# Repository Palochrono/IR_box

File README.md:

# IR_box
Normally open (HIGH) keychron low profile optical hitbox
Keychron switches footprint from [here](https://github.com/girishji/keychron-optical-keyboard?tab=MIT-1-ov-file)
## Part list
| Component | Description | Number_used |
| --------------- | --------------- | --------------- |
| R_IR | 180 $\Omega$ 0805 | 16 |
| R_PT | 2k $\Omega$ 0603 | 16 |
| Phototransistor | 0805 | 16 |
| IR_led | 0805 | 16 |
| Rp2040-zero | Waveshare | 1 |
| Pushbutton | 6*6mm | 4 |
| Key switches | Keychron optical low profile | 16 |
| OLED display | 0.96 inch I2C SSD1306 | 1 |
| Keycap set | DOIO KCGM-02 KCGM-03| 1 |
## Schematics and Render
Half-vias used to use the extra pins in rp2040-zero

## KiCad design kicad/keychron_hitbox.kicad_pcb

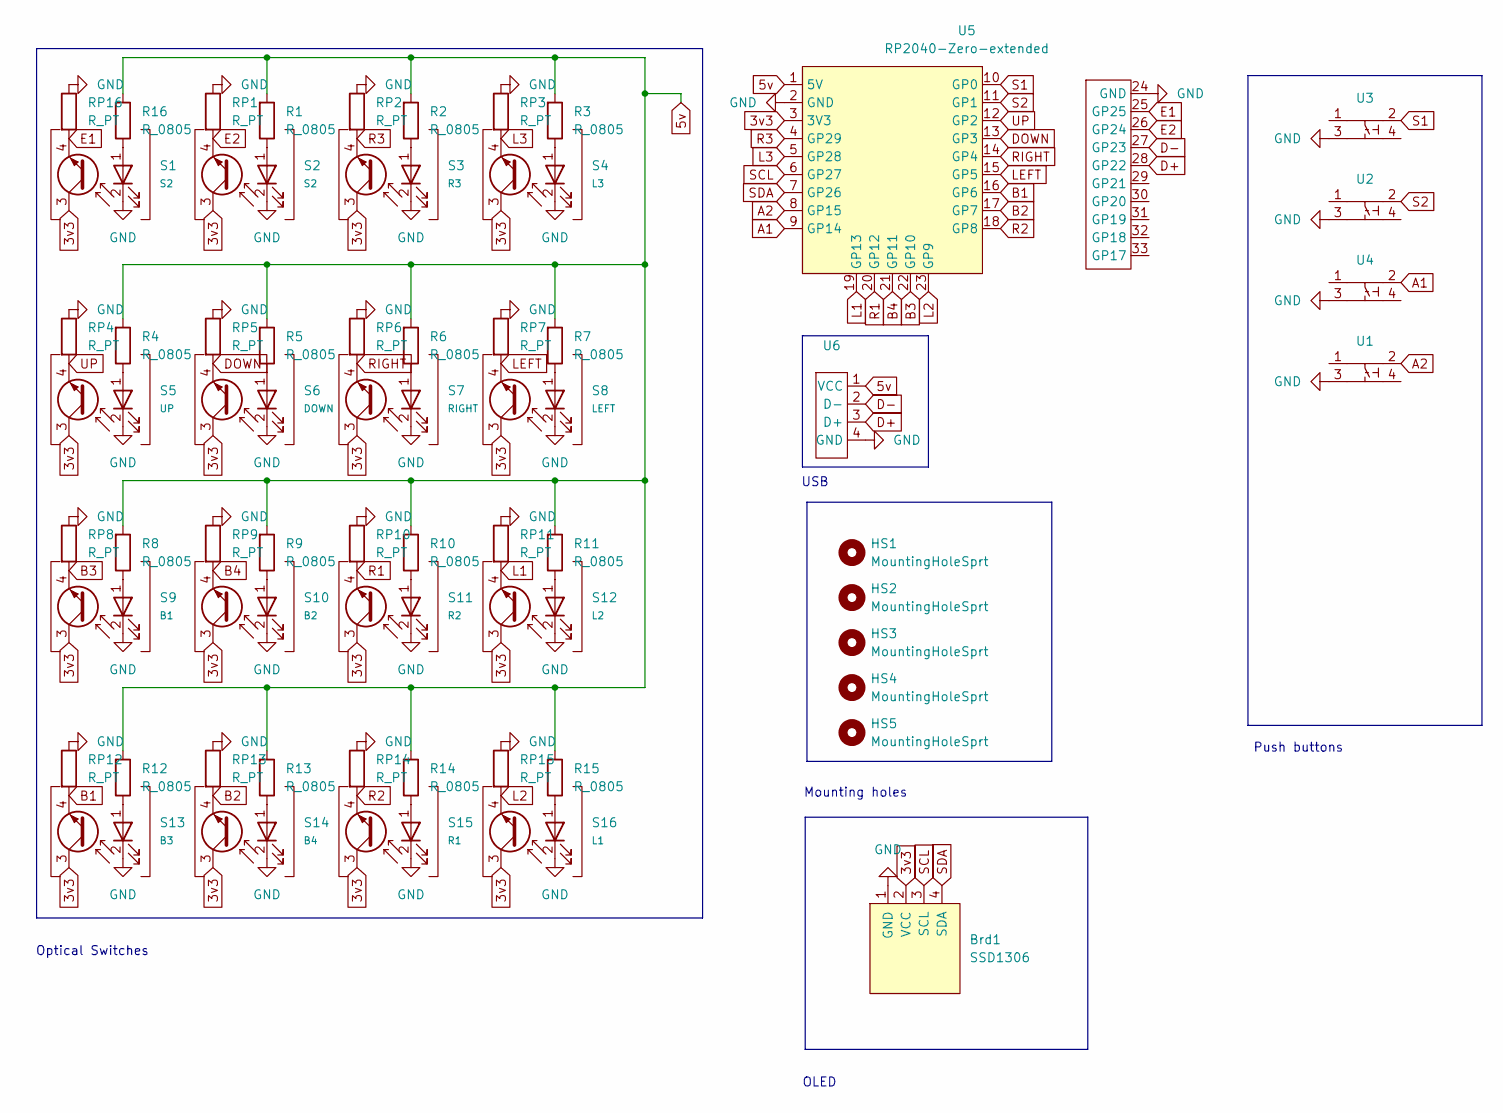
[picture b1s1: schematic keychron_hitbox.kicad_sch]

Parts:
Brd1: SSD1306; 128x64OLED_hollowed
HS1, HS2, HS3, HS4, HS5: MountingHoleSprt; MountingHole_2.2mm_M2_ISO7380_Pad
R1, R2, R3, R4, R5, R6, R7, R8, R9, R10, R11, R12, R13, R14, R15, R16: R_0805; R_0805_2012Metric
RP1, RP2, RP3, RP4, RP5, RP6, RP7, RP8, RP9, RP10, RP11, RP12, RP13, RP14, RP15, RP16: R_PT; R_0603; JLC 0805-2012
S1, S2: S2; Keychron_Optical_Switch_23mm
S3: R3; Keychron_Optical_Switch_23mm
S4: L3; Keychron_Optical_Switch_23mm
S5: UP; Keychron_Optical_Switch_26mm
S6: DOWN; Keychron_Optical_Switch_23mm
S7: RIGHT; Keychron_Optical_Switch_23mm
S8: LEFT; Keychron_Optical_Switch_23mm
S9: B1; Keychron_Optical_Switch_23mm
S10: B2; Keychron_Optical_Switch_23mm
S11: R2; Keychron_Optical_Switch_23mm
S12: L2; Keychron_Optical_Switch_23mm
S13: B3; Keychron_Optical_Switch_23mm
S14: B4; Keychron_Optical_Switch_23mm
S15: R1; Keychron_Optical_Switch_23mm
S16: L1; Keychron_Optical_Switch_23mm
U1, U2, U3, U4: 6x6pushbutton
U5: RP2040-Zero-extended; RP2040 Zero zllpin
U6: usba_header

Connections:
3v3: Brd1.2 (VCC), S1.3 (C), S2.3 (C), S3.3 (C), S4.3 (C), S5.3 (C), S6.3 (C), S7.3 (C), S8.3 (C), S9.3 (C), S10.3 (C), S11.3 (C), S12.3 (C), S13.3 (C), S14.3 (C), S15.3 (C), S16.3 (C), U5.3 (3V3)
5v: R1.1, R2.1, R3.1, R4.1, R5.1, R6.1, R7.1, R8.1, R9.1, R10.1, R11.1, R12.1, R13.1, R14.1, R15.1, R16.1, U5.1 (5V), U6.1 (VCC)
A1: U4.2, U5.9 (GP14)
A2: U1.2, U5.8 (GP15)
B1: RP12.2, S13.4 (E), U5.16 (GP6)
B2: RP13.2, S14.4 (E), U5.17 (GP7)
B3: RP8.2, S9.4 (E), U5.22 (GP10)
B4: RP9.2, S10.4 (E), U5.21 (GP11)
D+: U5.28 (GP22), U6.3 (D+)
D-: U5.27 (GP23), U6.2 (D-)
DOWN: RP5.2, S6.4 (E), U5.13 (GP3)
E1: RP16.2, S1.4 (E), U5.25 (GP25)
E2: RP1.2, S2.4 (E), U5.26 (GP24)
GND: Brd1.1 (GND), RP1.1, RP2.1, RP3.1, RP4.1, RP5.1, RP6.1, RP7.1, RP8.1, RP9.1, RP10.1, RP11.1, RP12.1, RP13.1, RP14.1, RP15.1, RP16.1, S1.2 (IR_K), S2.2 (IR_K), S3.2 (IR_K), S4.2 (IR_K), S5.2 (IR_K), S6.2 (IR_K), S7.2 (IR_K), S8.2 (IR_K), S9.2 (IR_K), S10.2 (IR_K), S11.2 (IR_K), S12.2 (IR_K), S13.2 (IR_K), S14.2 (IR_K), S15.2 (IR_K), S16.2 (IR_K), U1.3, U2.3, U3.3, U4.3, U5.2 (GND), U5.24 (GND), U6.4 (GND)
L1: RP11.2, S12.4 (E), U5.19 (GP13)
L2: RP15.2, S16.4 (E), U5.23 (GP9)
L3: RP3.2, S4.4 (E), U5.5 (GP28)
LEFT: RP7.2, S8.4 (E), U5.15 (GP5)
unnamed: R16.2, S1.1 (IR_A)
unnamed: R1.2, S2.1 (IR_A)
unnamed: R2.2, S3.1 (IR_A)
unnamed: R3.2, S4.1 (IR_A)
unnamed: R4.2, S5.1 (IR_A)
unnamed: R5.2, S6.1 (IR_A)
unnamed: R6.2, S7.1 (IR_A)
unnamed: R7.2, S8.1 (IR_A)
unnamed: R8.2, S9.1 (IR_A)
unnamed: R9.2, S10.1 (IR_A)
unnamed: R10.2, S11.1 (IR_A)
unnamed: R11.2, S12.1 (IR_A)
unnamed: R12.2, S13.1 (IR_A)
unnamed: R13.2, S14.1 (IR_A)
unnamed: R14.2, S15.1 (IR_A)
unnamed: R15.2, S16.1 (IR_A)
R1: RP10.2, S11.4 (E), U5.20 (GP12)
R2: RP14.2, S15.4 (E), U5.18 (GP8)
R3: RP2.2, S3.4 (E), U5.4 (GP29)
RIGHT: RP6.2, S7.4 (E), U5.14 (GP4)
S1: U3.2, U5.10 (GP0)
S2: U2.2, U5.11 (GP1)
SCL: Brd1.3 (SCL), U5.6 (GP27)
SDA: Brd1.4 (SDA), U5.7 (GP26)
UP: RP4.2, S5.4 (E), U5.12 (GP2)

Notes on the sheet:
USB
Push buttons
Optical Switches
Mounting holes
OLED

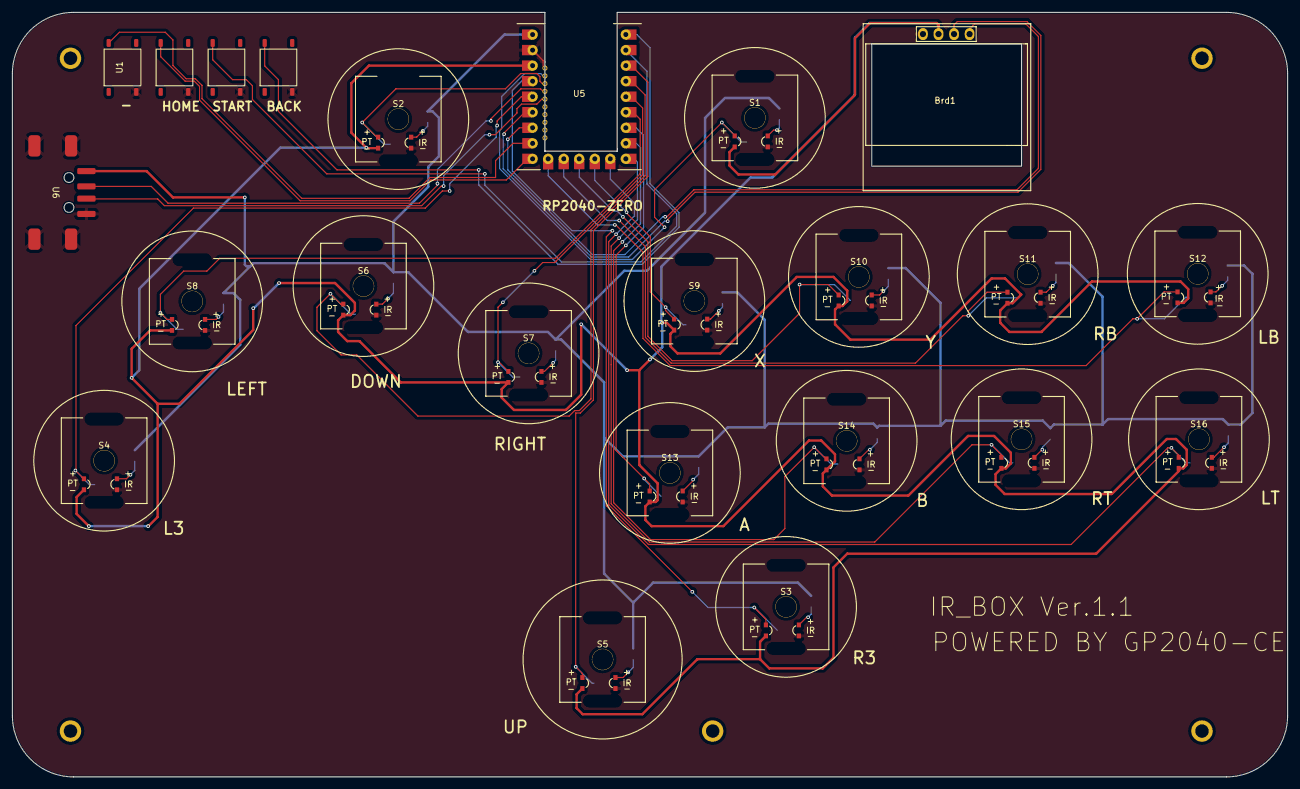
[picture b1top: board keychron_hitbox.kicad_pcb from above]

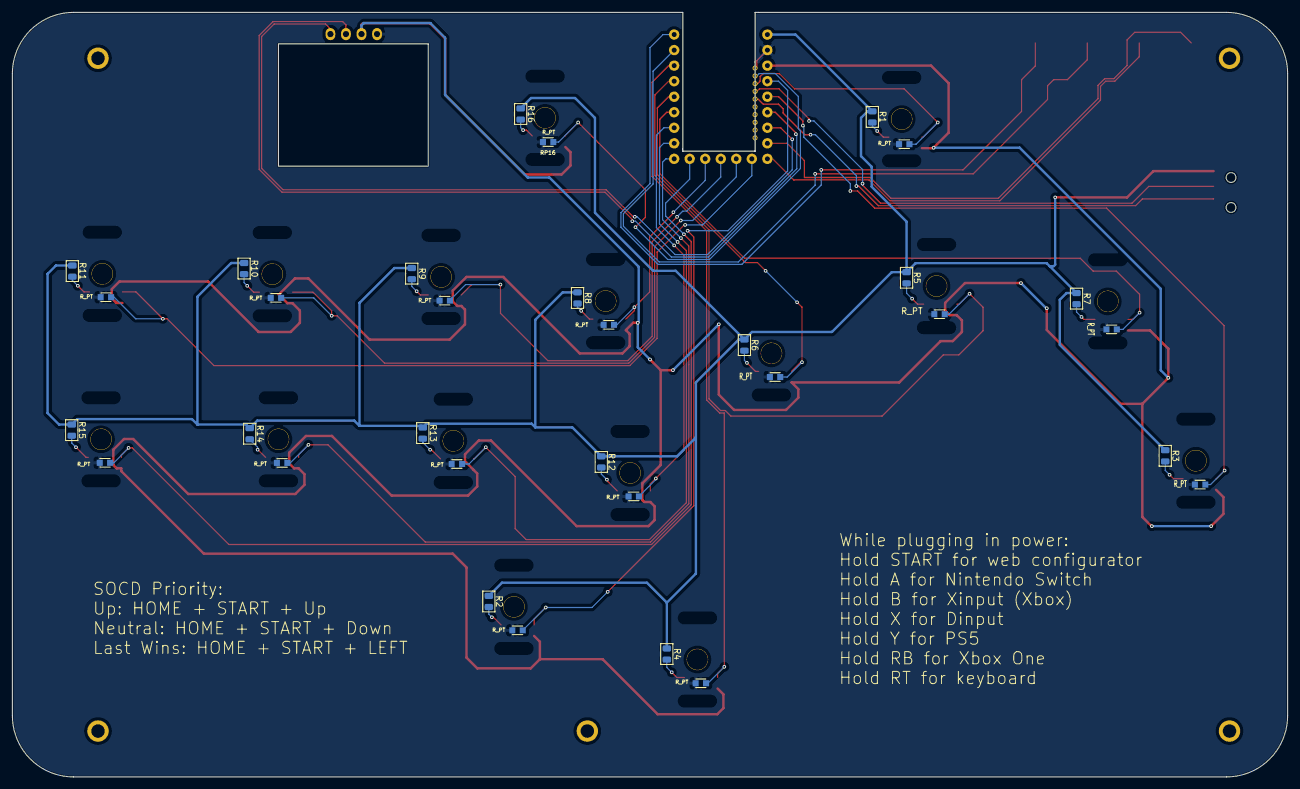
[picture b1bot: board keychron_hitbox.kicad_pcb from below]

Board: 2 copper layers, 208.5 x 125.0 mm, 60 parts (32 on the bottom side), 43 nets.

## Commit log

2024-11-09 initial upload
2024-11-14 updated seating for OLED & some acrylic designs
2024-11-20 adding version 1.1
2024-12-05 fix 3d file keyswitch plate
